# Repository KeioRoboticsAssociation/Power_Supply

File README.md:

# 電源基板
## 経緯
ロボットによく使う電源をまとめて出力できる基板があると便利という話があったので作りました。

## 仕様

使っている素子の詳しいことは以下のデータシートを読みましょう。  
[OKL-T/6-W12](http://akizukidenshi.com/download/ds/murata/OKL_T6_W12.pdf)  
[TA48033S](http://akizukidenshi.com/download/ta48033s.pdf)

|コネクタ|機能|
|:-|:-|
|P1|12V出力(XT60コネクタ・オス)|
|P2|12V出力(DCコネクタ・メス)|
|P3・P4|5V出力(DCコネクタ・メス), 合計6Aまで|
|P5・P6|3.3V出力(DCコネクタ・メス), 合計1Aまで|
|P7|12V入力(XT60コネクタ・オス)|

DCDCコンバータ(U1)は表面実装なので少しはんだ付けが難しい。なので5V電源に要求される電流が少ない場合、3端子レギュレータを代わりに実装できるようにスルーホールも開けてある。

DCDCコンバータを使う場合は、10Ω, 330Ω, 1kΩの3つの抵抗の合計値を変更すれば、出力電圧を0.591V〜5.5Vの範囲で変更できる。値の変え方はデータシートに書いてある。

THROUGH端子(P1・P2)は内部的には電源入力端子と同じなので、実は電源入力端子としても使える。例えばパソコンのACアダプタをP2に繋いで5V電源を取り出したり出来る。

## 部品表
|番号|部品名|個数|備考|
|:-|:-|:-|:-|
|P1,P7|XT60オス|2|オス・メスを間違えやすいので気をつけて。ラジコンショップで売ってる|
|P2,P3,P4,P5,P6|基板取り付け用DCジャック|5|センタープラス。|
|C1|22uF, 16V|1|電解コンデンサ|
|C2|(0.33uF)|0|U2のセットに含まれてるので買わなくて良い。|
|C3|(33uF)|0|U2のセットに含まれてるので買わなくて良い。|
|C4|10uF, 16V|1|電解コンデンサ|
|D1・D2|3mm赤色LED 70° OSR5JA3Z74A|2|別にこれじゃなくてもいい。|
|U1|DCDCコンバータ OKL-T/6-W12|1|表面実装のやつ。|
|U2|TA48033S|1セット|コンデンサがセットになってるやつが秋月で売ってる。|
|抵抗|抵抗値は基板に書いてある|合計5個||

※注意：はんだ付けするときは背の低い部品からつけていくと良い。U1は最初につけるべし。

## イメージ

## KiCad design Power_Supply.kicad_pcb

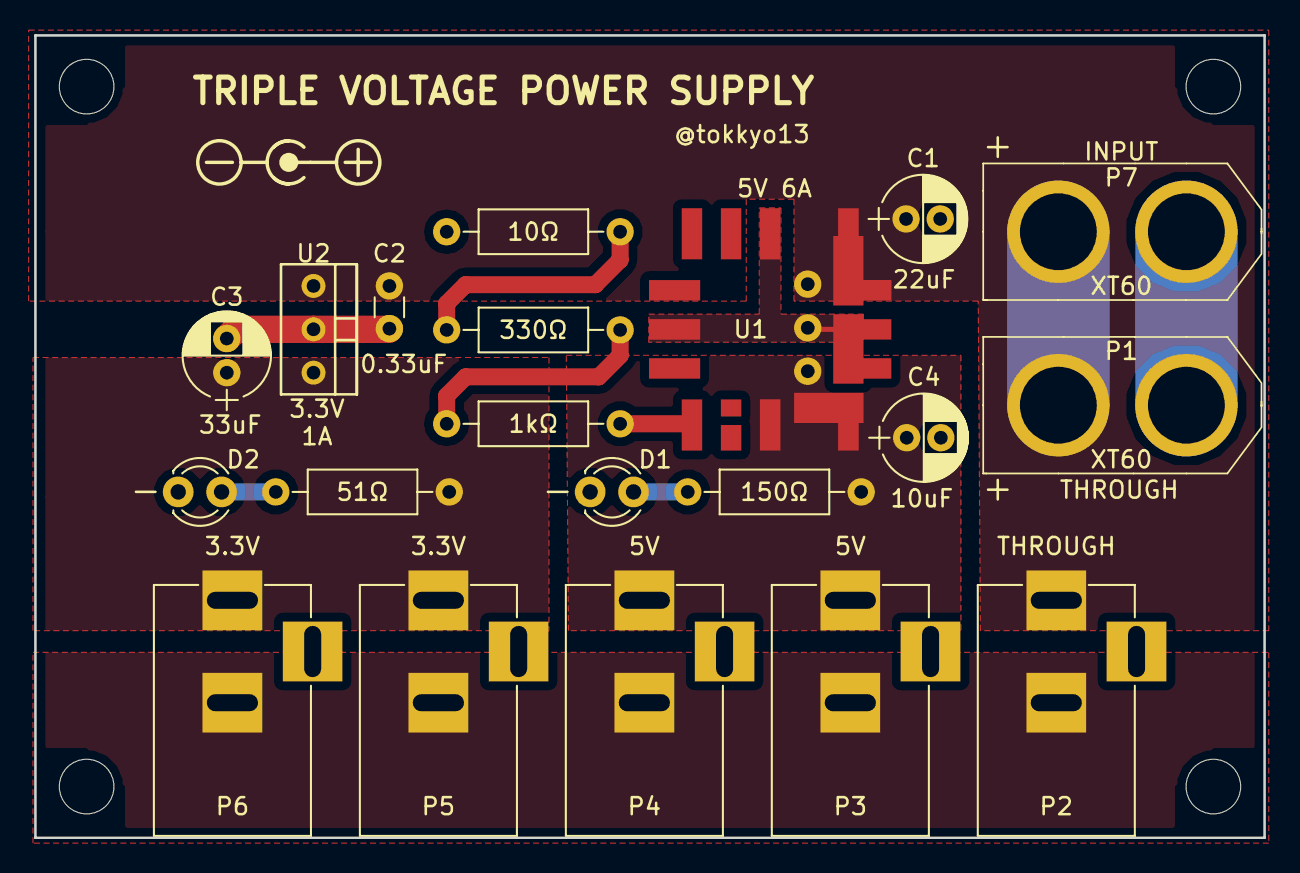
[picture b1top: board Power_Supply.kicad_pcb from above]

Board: 2 copper layers, 72.0 x 47.0 mm, 20 parts (0 on the bottom side), 9 nets.

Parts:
1kΩ: 1k; R_Axial_DIN0207_L6.3mm_D2.5mm_P10.16mm_Horizontal
10Ω: 10; R_Axial_DIN0207_L6.3mm_D2.5mm_P10.16mm_Horizontal
51Ω: 51; R_Axial_DIN0207_L6.3mm_D2.5mm_P10.16mm_Horizontal
150Ω: 150; R_Axial_DIN0207_L6.3mm_D2.5mm_P10.16mm_Horizontal
330Ω: 330; R_Axial_DIN0207_L6.3mm_D2.5mm_P10.16mm_Horizontal
C1: 22uF; CP_Radial_D5.0mm_P2.00mm
C2: 0.33uF; C_Disc_D3.0mm_W1.6mm_P2.50mm
C3: 33uF; CP_Radial_D5.0mm_P2.00mm
C4: 10uF; CP_Radial_D5.0mm_P2.00mm
D1, D2: LED; LED_D3.0mm
P1, P7: CONN_01X02; XT60
P2, P3, P4, P5, P6: CONN_01X02; BARREL_JACK
U1: OKL-T/6-W12; DCDC-murata-6A
U2: NCP1117ST33T3G; OldSowjetaera_Transistor_Type-I_SmallPads

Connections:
GND: 10Ω.2, C1.2, C2.2, C3.2, C4.2, D1.1, D2.1, P1.1, P2.2, P3.2, P4.2, P5.2, P6.2, P7.2, U1.1, U1.3, U1.7, U2.1
unnamed: 150Ω.1, D1.2
unnamed: 51Ω.1, D2.2
unnamed: 1kΩ.1, U1.6
unnamed: 1kΩ.2, 330Ω.1
unnamed: 10Ω.1, 330Ω.2
V3.3: 51Ω.2, C3.1, P5.1, P6.1, U2.2
V5: 150Ω.2, C4.1, P3.1, P4.1, U1.4, U1.5
V12: C1.1, C2.1, P1.2, P2.1, P7.1, U1.2, U2.3

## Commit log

2017-10-01 add new files
2017-10-01 add new picture
